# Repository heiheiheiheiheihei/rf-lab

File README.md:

# RF-LAB · 百元射频实验室

**丰俭由人:¥100 的固定码侦察包 → ¥999 的全频段工作台。**
一块 ESP32-C3,五个可换射频舱位;同一套命令契约延伸到 **Web / Android / uConsole /
OPPO Watch 2**,与官网共用一套视觉基线([`docs/01-ui.md` §5.1](docs/01-ui.md))。
现役链路是 **YS-RF34DL 315/433 固定码**;CC1101 / NRF24L01 / SI4463 / LR1121、
MQTT 与 Home Assistant 是路线图,不是现货能力。

[**官网 / 配装台(线上)**](https://heiheiheiheiheihei.github.io/rf-lab/) · [**下载 Android APK**](https://github.com/heiheiheiheiheihei/rf-lab/releases/latest/download/rf-lab-android.apk) · [**OPPO Watch 2 客户端**](watch/README.md) · [**下载 Watch APK**](https://github.com/heiheiheiheiheihei/rf-lab/releases/download/watch-v0.1.0/rf-lab-watch.apk) · [本地源](site/index.html) · [文档索引](docs/README.md) · [射频规格](docs/00-mvp.md) · [UI 规格](docs/01-ui.md) · [接线](hardware/README.md) · [官网维护说明](site/README.md)

## ¥100 → ¥999:先买一块能用的板

| 档位 | 预算 | 组成 | 能力 |
|---|---:|---|---|
| 侦察兵 SCOUT | ¥100 | CORE-C3 + YS-RF34DL | 315/433 固定码学习 / 回放(**现役,已上机**) |
| 突击手 ASSAULT | ¥299 | + CC1101 + NRF24L01 + 背板 + 天线包 | Sub-GHz + 2.4G(路线图) |
| 战术组 TACTICAL | ¥599 | + SI4463 + LR1121 + 收纳盒 | 全频段雏形(路线图) |
| 全频段 ALL-IN | ¥999 | 全模块 + FIELD DOCK | 全舱位 / 现场终端(路线图) |

> 价格为**参考物料价**,不含运费与工具;路线图模块未接入现役固件,不能下单即用。
> 交互式配装器:[`site/index.html`](site/index.html);预算/边界/发布说明:[`site/README.md`](site/README.md)。

### 射频模块

| 模块 | 频段 | 接口 | 角色 | 状态 |
|---|---|---|---|---|
| **YS-RF34DL** | 315 / 433 MHz | UART 9600 | 固定码学习 / 回放 | ✅ **现役,上机验证** |
| CC1101 | 300–928 MHz | SPI | Sub-GHz 通用收发 | ○ 路线图,未接入 |
| NRF24L01+ | 2.4 GHz | SPI | 2.4G 私有链路 | ○ 路线图,未接入 |
| SI4463 | 119–1050 MHz | SPI | 远距 / 窄带 | ○ 路线图,未接入 |
| LR1121 | Sub-GHz + 2.4G | SPI | 双频 LoRa / (G)FSK | ○ 路线图,未接入 |

> 配装器可以勾选路线图模块,那是**采购与规划**,不是固件能力。只有 YS-RF34DL 做过上机验证。

## 现役链路

两块板:**ESP32-C3 OLED** + **YS-RF34DL** 315/433 编解码模块。
按一下原遥控器 → 模块解码 → ESP32 存码 → 板载 OLED 显示状态 → **Web / BLE / 串口 / uConsole**
发射 → 原接收器动作。

硬件文档与官网视觉是**抽象接线图**(不画 3D/写实 PCB):只保留两块功能块、4 根线和必须正确的引脚;
可选的 PCB 底板另见 [`hardware/pcb/`](hardware/pcb/README.md)(已出 Gerber,未打样)。
唯一源是 [`hardware/wiring.json`](hardware/wiring.json);`tools/gen_wiring.py` 同时生成
`firmware/src/wiring_config.h`、`hardware/README.md` / `docs/00-mvp.md` 的接线表和
4 张 SVG,`gen_wiring.py --check` 在主机测试与固件构建前校验一致性。
官网 §01 用宽图(窄屏切竖图)、§02 放主控/模块引脚图;设备 UI 顶栏 `HW` 芯片(或按 `H`)
打开同一张图,`ZOOM/FIT` 缩放。
**3.3V ONLY**、共地、`GPIO3→RXD` / `GPIO4←TXD` 由接线表保证;图不是比例图,
引脚/供电仍以 [`hardware/README.md`](hardware/README.md) 为准。参考照片不入库。

同一块 C3 现在同时提供:

| 入口 | 形态 | 说明 |
|---|---|---|
| **Web** | LAN IP(STA)或 `http://192.168.4.1/`(AP 回退) | 板载 HTTP + SSE,手机/PC/uConsole 浏览器直接用 |
| **Android** | BLE APK | 同一份单页 UI 跑在 WebView,原生 BLE 桥 |
| **OPPO Watch 2** | 独立 BLE APK | 402×476 单屏;ARM → SEND;按住 HOLD → LONG,松手 STOP;46mm 真机已验证 |
| **uConsole** | 键盘 TUI | `rflab-tui`,HTTP 优先、USB 串口回退,琥珀/橄榄战术风 |
| **串口** | `tools/rf34dl.py` | 0.5.0 既有命令行,行为不变 |

### 手腕上的发射键

OPPO Watch 2 客户端把手机端的「选码 → ARM → SEND」压缩成一屏:码卡上下滑换码,
`SEND` 单发,`HOLD` 按住 350ms 才发 `LONG`、松手立刻 `STOP`;断链/退后台先停。
它只走 BLE,复用同一套 GATT/行协议,**不改固件、不改手机 APP**。

- 46mm `OW20W1` / Android 8.1 (API 27) / 402×476 @320dpi 真机已验证:安装、扫描、
  PIN、32 码、ARM/SEND、HOLD/LONG/STOP、错误 PIN、退后台 STOP、OLED TEST。
- 独立 **release key** 签名(不与手机 APK 共用);debug → release 需卸载后重装。
- 公开 Release:[**下载 rf-lab-watch.apk**](https://github.com/heiheiheiheiheihei/rf-lab/releases/download/watch-v0.1.0/rf-lab-watch.apk) ·
  [`SHA256SUMS.txt`](https://github.com/heiheiheiheiheihei/rf-lab/releases/download/watch-v0.1.0/SHA256SUMS.txt)
- 规格与安装:[`watch/README.md`](watch/README.md) · 证据:[`docs/evidence/2026-11-22-watch-release.md`](docs/evidence/2026-11-22-watch-release.md)

**Wi-Fi 模式**:有凭据先 `STA-only` 接局域网(AP 关闭);15s 连不上自动打开 AP 回退;
AP 下可以直接用,也可以重新配网或 `WIFI CLEAR`。AP 里配网成功会保持 AP,避免踢掉
正在配网的浏览器;下次启动再回到 STA-only。

- **射频/命令唯一规格**:[`docs/00-mvp.md`](docs/00-mvp.md)
- **跨平台 UI 规格**:[`docs/01-ui.md`](docs/01-ui.md)
- **接线**:[`hardware/README.md`](hardware/README.md)(模块 4 根线;引脚权威)
- **固件**:[`firmware/README.md`](firmware/README.md)(ESP-IDF 5.5.5 / ESP32-C3)
- **Android**:[`android/README.md`](android/README.md) · **uConsole**:[`uconsole/README.md`](uconsole/README.md) · **Watch**:[`watch/README.md`](watch/README.md)

## 官网 / 配装台

线上:<https://heiheiheiheiheihei.github.io/rf-lab/>(GitHub Pages / GitHub Actions 发布 `site/`)。

[`site/index.html`](site/index.html) 是静态单页:4 档预算、9 个模块勾选、实时配装单、
**内嵌真实单页 UI 的交互终端 demo**、OPPO Watch 2 实机区、MQTT/HA 路线图。
无站点构建、无外部字体、无 CDN、无外部/API 请求。

§03 终端区直接跑 `web/` 的真实 UI(iframe):可以 ARM、SEND、LONG、STOP、ERASE,也可以用
「模拟遥控器」学习一条新码;`site/assets/terminal-demo.js` 在 iframe 内接管
`fetch`/`EventSource`,本地回放 `/api/*` 与 SSE,只标 `SIM`,不发网络请求、不代表真机在线。

```bash
python3 tools/gen_wiring.py --check    # JSON -> 代码头/表/SVG 一致性
python3 tools/build_web.py             # 同步生成 site/assets/terminal.html
python3 -m http.server 8088 -d site    # http://127.0.0.1:8088/
python3 tools/site_check.py            # 静态验收(含 demo 资源)
node --check site/app.js
node --check site/assets/terminal-demo.js
```

## 快速开始

```bash
export PATH="$HOME/.platformio/penv/bin:$PATH"

# 1) 构建 + 烧录(必须用 flash.sh:它会一起写 2MB 分区表)
./tools/flash.sh /dev/ttyACM0

# 2) Web:
#    有 STA 凭据:设备先连局域网;成功用串口 INFO / OLED 显示的 LAN IP 访问。
#    无凭据或 15s 连不上:连 AP "RF-Lab-XXXX" / 密码 rflab1234,打开 http://192.168.4.1/
#    AP 设置页填 SSID/PASSWORD 配网;FORGET/AP 清除凭据。
#    串口会打印 AP SSID/IP、BLE PIN;OLED 开机页也显示 PIN / LAN / AP 状态。

# 3) 串口交互(既有)
python3 tools/rf34dl.py --port /dev/ttyACM0
python3 tools/rf34dl.py --port /dev/ttyACM0 learn 15
python3 tools/rf34dl.py --port /dev/ttyACM0 send 1

# 4) uConsole 键盘 TUI
./uconsole/install.sh
rflab-tui --url http://192.168.4.1   # 若已接 LAN,换成 INFO/OLED 的 LAN IP

# 5) Android(已装 JDK/SDK/Gradle 时)
python3 tools/build_web.py
cd android && ./gradlew assembleDebug

# 6) OPPO Watch 2(独立 release key,见 watch/README.md)
set -a; . "$HOME/.config/rf-lab/watch-keystore.env"; set +a
./watch/check.sh
cd watch && ../android/gradlew assembleRelease
# android/app/build/outputs/apk/debug/app-debug.apk
```

主机单测:`./tools/host_test.sh`(协议 76 + 码库 368 + 事件环 9,427 + OTA 41 + radio 114 + OLED/UI 1,286 + TUI 12)。
APP 自更新逻辑主机测试:`./tools/app_update_test.sh`(版本比较 + `SHA256SUMS` 查表,36 checks)。
Wi-Fi 回退上机自检:`python3 tools/wifi_selftest.py --port /dev/ttyACM0`(15 项)。

## 状态

| 项 | 状态 |
|---|---|
| 构建 | ✅ v0.7.2 tag `e0f155a`:**1,126,928B / 2,031,616B(55.5%)**,RAM 90,260B(27.5%);master M1a(`f55126f`):**1,128,400B(55.5%)**,RAM 90,308B(27.6%),未上机 |
| 主机单测 | ✅ C 测试 **11,312** checks(协议 76 + 码库 368 + 事件环 9,427 + OTA 41 + radio 114 + OLED/UI 1,286);另有 TUI 12、selftest 18、APP 自更新 36 |
| 上机:学码 / 存码 / 改波特率 | ✅ 2026-11-15(0.5.0 证据) |
| 上机:发射 `SEND/LONG/STOP` | ⚠️ 2026-11-15 有 `F0/FE/FF`;2026-11-21 模块命令方向 0 应答;11-22 `MODE` 回 `F2`,但 **`SEND` 未复测** |
| 上机:Wi-Fi | ✅ 真实 `SSID-A`→`192.168.5.117`;AP 回退 15/15;AP 配网 / `WIFI CLEAR`;⏳ AP 外部浏览器、STA 运行中掉线 |
| 上机:Web | ✅ HTTP/SSE/POST + 真实 Chromium 无 console error;⏳ 新皮肤全量回归 |
| 上机:BLE | ✅ 真机连接/鉴权/命令回显/码表/状态栏(2026-11-21);⏳ BLE `SEND`、错误 PIN |
| Android APK | ✅ **0.7.2 已发** [Release](https://github.com/heiheiheiheiheihei/rf-lab/releases/tag/v0.7.2);1,050,272B/versionCode 4/v2;✅ 0.7.1 真机安装/自更新;⏳ 0.7.2 真机安装 |
| APP 自更新 | ✅ 36 checks + 真实 Release 资产;✅ 真机弹窗/下载/系统安装器/覆盖安装(0.7.0→0.7.1);⏳ 失败路径 |
| 码库 v2 | ✅ 21/64;迁移/UTF-8/新建/编辑/删除;✅ BLE `NAME/GROUP/SYM/EDIT` 写入;⏳ 写后重启持久化 |
| OTA | ✅ 双槽 A→B→A + 错 token/坏镜像/断流;⏳ 浏览器上传、崩溃回滚、AP、真断电 |
| uConsole TUI | ✅ 主机解析/键位/PTY;⏳ 真机 |
| 官网 | ✅ 交互 demo + Pages 部署;⏳ 线上交互回归 |
| 官网 APK 入口 | ✅ 指向 `releases/latest/download`;⏳ 真机下载安装 |
| UI 一键固件更新(0.7.3) | ○ **未实现**;BOOT 确认 + GitHub Pages + 设备 SHA-256;见 [`docs/01-ui.md`](docs/01-ui.md) §3.4.1 |
| 路线图 | ○ MQTT / HA / 多模块未实现,接口草案见官网 §04 |
| 距离 / 长发时接收器 | ⏳ 未测,见规格 §7 |
| 上机证据 | [`2026-11-22-release-0.7.2.md`](docs/evidence/2026-11-22-release-0.7.2.md) · [`2026-11-22-app-ble.md`](docs/evidence/2026-11-22-app-ble.md) · [`2026-11-21-ota.md`](docs/evidence/2026-11-21-ota.md) · [`2026-11-15-bringup.md`](docs/evidence/2026-11-15-bringup.md) · [`2026-11-15-wifi-lan.md`](docs/evidence/2026-11-15-wifi-lan.md) |

> 完整测试登记、优先级与 gate 见 [`docs/02-plan.md`](docs/02-plan.md) §3;新会话交接见 [`docs/03-execution.md`](docs/03-execution.md)。

## 范围

| 做 | 不做 |
|---|---|
| 315/433 固定码学习 / 解码 / 存 / 发 | 滚动码克隆 / 重放 |
| 单次发射、长发 / 停止 | 原始 OOK 波形记录(0.7.x) |
| 码库命名/分组/手工建码/改 band+4B code | 协议位解析 / 模块 TX 时长编辑 / `.sub` 导入(0.7.x;0.8.x 只读见 ADR-003) |
| 改模块波特率 / 输出模式 | 扫频 / RSSI / 频谱 |
| Wi-Fi STA 接 LAN + AP 回退(HTTP + SSE) | 公网/云账户 |
| 双槽 OTA(Web/串口,整包含页面) | BLE 上传固件 / 云推送 / 固件签名校验 |
| APP 自更新(GitHub Release,一键/忽略) | 静默安装 / 应用商店分发 |
| BLE 外设 + Android APP | BLE 链路加密(只有应用层 PIN) |
| uConsole 键盘 TUI | OLED 菜单/按键交互 |
| 串口 / OLED 状态页(既有,保留) | OLED 中文/图形界面 |
| 官网 / ¥100–999 配装规划(静态) | 把配装器里的路线图模块写成已支持 |
| 自有固定码设备的复制验证 | 对未知设备的"安全"断言 |

> ⚠️ 固定码本身可被复制:测试只对**自有**设备做,结论只对固定码成立。
> Web 的 `ARM` 只防误触,不是发射硬门控;**HTTP 无登录,AP 密码/局域网可达性是门槛**;
> BLE 只有 4 位应用层 PIN,不是强安全边界。

## 版本计划

| 版本 | 目标 | 状态 |
|---|---|---|
| 0.7.3 | UI 一键固件更新:查 Pages manifest、BOOT 确认、下载/校验/上传 | ○ 规划,见 [`docs/01-ui.md`](docs/01-ui.md) §3.4.1 |
| 0.8.0 | 模块抽象层 + SPI 背板;CC1101 首发,NRF24/SI4463/LR1121 分批(0.8.x) | ○ 设计目标;M1a HAL 仅主机/构建 |
| 0.9.0 | 本地 MQTT bridge + Home Assistant Discovery | ○ 设计目标 |
| 1.0 | 多模块外壳 / 小批量 | ○ 设计目标 |

> 官网 §04 的 MQTT / HA 拓扑与 topic 是**接口草案**,不是可售能力。
> 现在只有 HTTP/SSE + BLE/串口;不要提前写“支持 Home Assistant”。

## 截图

官网 §03 的交互终端(真实单页 UI,传输为本地模拟):

设备 UI 的硬件模态(本地 Chromium mock)与真实 LAN 页面(0.6.0 旧皮肤,非 mock):

更多 mock 布局图在 [`docs/evidence/`](docs/evidence/);截图不是上机证据,上机结论只以 evidence 的 md/log 为准。

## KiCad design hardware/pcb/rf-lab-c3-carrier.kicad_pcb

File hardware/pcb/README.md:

# RF-Lab C3 底板 v1.0

**状态:设计完成、DRC/ERC 通过、Gerber 已导出;未打样、未上机。** 2026-11-23

一块 60 × 80 mm、2 层、全直插的“插座底板”,把现在用杜邦线吊着的
**01Space ESP32-C3-0.42LCD** 和 **YS-RF34DL 315/433 MHz 模块**固定成两块可插拔的板:
C3 板插在左侧 2×7/8 母座上,射频模块插在 J3 母座上,两者都能直接拔换。

> 尺寸在嘉立创免费打板范围内(≤100×100 mm、2 层、绿油、HASL、5 片)。
> **打样前务必打印 [`fab/check-1to1.pdf`](fab/check-1to1.pdf) 按 100% 比例,把 C3 板压上去核对插座孔位。**

| 项目 | 值 |
|---|---|
| 板尺寸 | 60.0 × 80.0 mm,2 层,1.6 mm,1 oz |
| 工艺 | 绿油白字、HASL、无铅(嘉立创免费档) |
| 连接器 | 全 2.54 mm 直插;J1/J2/J3 母座,J4/J5 公排针 |
| 安装 | 4 × M2.5 NPTH(2.7 mm),2 × 2.1 mm 天线/扎带孔 |
| 供电 | 仅 3.3 V;由 C3 板的 3V3 引脚供给模块,板上无稳压器 |
| 额外 | C1 10 µF + C2 100 nF(0805,3V3 去耦,可选) |
| 铜 | 双面 GND 铺铜 + 10 个缝合过孔;信号/电源走线 0.25–0.5 mm |

## 1. 它解决什么问题

现役接法是 C3 板 + 4 根杜邦线 + 模块,换模块/换板都要重新插线,还容易把
VCC/GND 插反。底板把 4 根线固化:

- **C3 板可拔**:两个标准 2.54 母座(1×7 + 1×8),不用焊死在底板上。
- **模块可拔**:J3 是 1×4 母座,模块直接插;旁边 J4 再引一组同样的
  `3V3/GND/IO3/IO4`,接别的串口模块时不用改板。
- **所有剩余 GPIO 引出**:J5(1×16)把 11 个 GPIO 和 3V3/5V/BAT/GND 全部引出。
- **嘉立创免费档**:60×80 mm、2 层、全直插,不需要 SMT 贴片。

## 2. 接口与引脚

### 2.1 C3 插座 J1 / J2(面向底板,USB 朝上)

| 位置 | 1 | 2 | 3 | 4 | 5 | 6 | 7 | 8 |
|---|---|---|---|---|---|---|---|---|
| **J1(8 pin,右列)** | BAT | 5V | GND | 3V3 | IO20 | IO21 | IO0 | IO1 |
| **J2(7 pin,左列)** | IO10 | IO8 | IO7 | IO6 | IO5 | IO4 | IO3 | — |

- 两排**中心距 15.24 mm**(6 × 2.54),针距 2.54;两排**在 Qwiic 端对齐**,
  8 pin 排在 USB 端多出一针 —— 与 01Space 原板一致。
- J1/J2 的 **1 脚是方焊盘**,靠 USB 端;插反了 C3 板的 BAT 会落到 5V 上。
- 丝印已把每一针的网名印在插座外侧;插上 C3 板后仍可见。

### 2.2 模块座 J3(1×4 母座)

| 针 | 1 | 2 | 3 | 4 |
|---|---|---|---|---|
| 网名 | **3V3** | **IO4** | **IO3** | **GND** |
| 模块侧 | VCC | TXD | RXD | GND |

模块的 4 针顺序按你确认的 **VCC → TXD → RXD → GND**(从正面、天线端数)。
交叉关系:**模块 TXD(2)→ C3 的 IO4(RX)**,**模块 RXD(3)← C3 的 IO3(TX)**。

> **接反 VCC/GND 会烧模块。** 上电前用万用表量 J3.1–J3.4 应为 3.3 V;
> 若你的模块丝印顺序不是 VCC/TXD/RXD/GND,**不要插 J3**,改用 J4 飞线。

### 2.3 备用座 J4(1×4 公排针)

| 针 | 1 | 2 | 3 | 4 |
|---|---|---|---|---|
| 网名 | 3V3 | GND | IO3 | IO4 |

### 2.4 全引出 J5(1×16 公排针)

| 针 | 1 | 2 | 3 | 4 | 5 | 6 | 7 | 8 |
|---|---|---|---|---|---|---|---|---|
| 网名 | IO3 | IO4 | IO5 | IO6 | IO7 | IO8 | IO10 | GND |

| 针 | 9 | 10 | 11 | 12 | 13 | 14 | 15 | 16 |
|---|---|---|---|---|---|---|---|---|
| 网名 | IO1 | IO0 | IO21 | IO20 | 3V3 | 5V | BAT | GND |

- 1 脚方焊盘在**左侧**(靠近 J2)。
- 11 个 GPIO 全部引出;IO20/IO21 同时是 UART0 控制台,引出不影响现役固件。
- **BAT 是电池输入脚**,不是稳压输出;不要把它当 3.3 V 源。

### 2.5 与 `hardware/wiring.json` 的关系

`gen_pcb.py` 启动时会读 `../wiring.json`,断言 `module_tx=3`、`module_rx=4`、
`console=20/21`、`oled=5/6`;改接线先改 JSON,再重跑生成器。PCB 的 4 根模块线
不是第二套定义。

## 3. BOM(全部可手焊)

| 位号 | 规格 | 数量 | 备注 |
|---|---|---|---|
| J1 | 2.54 mm 1×8 **母座** | 1 | 可用 1×40 排母剪 |
| J2 | 2.54 mm 1×7 **母座** | 1 | 同上 |
| J3 | 2.54 mm 1×4 **母座** | 1 | 模块座 |
| J4 | 2.54 mm 1×4 **公排针** | 1 | 备用模块口 |
| J5 | 2.54 mm 1×16 **公排针** | 1 | 全引出 |
| C1 | 10 µF 16 V X5R 0805 | 1 | 可选,3V3 储能 |
| C2 | 100 nF 50 V X7R 0805 | 1 | 可选,去耦 |
| H1–H4 | M2.5 螺丝/铜柱 | 4 | 2.7 mm 孔 |
| — | 17–23 cm 单芯天线 | 1 | 焊在模块天线焊盘 |

CSV:[`fab/bom.csv`](fab/bom.csv)。

## 4. 装配顺序

1. 先焊 J1、J2、J3 三个**母座**,再焊 J4、J5 两个公排针;最后焊 C1/C2(可选)。
2. 断电,万用表检查:
   - J3.1–J3.4 之间**不能短路**;
   - J1.3(GND)与 J1.4(3V3)之间不能短路;
   - J5.8 / J5.16 与 J1.3 通。
3. 把 C3 板插进 J1/J2:**USB 朝底板的上边缘**,J1 的方焊盘对 C3 的 BAT 针。
4. 上电(USB),量 J3.1 对 J3.4 应为 **3.3 V**。
5. 断电,插模块(J3.1=VCC),接天线,再上电。
6. 用 `INFO` / 串口确认模块有应答;第一次不要直接长发射。

**禁止**:5 V 进 J3.1 或 C3 的 GPIO;不接天线长时间发射;带电插拔模块。

## 5. 嘉立创免费打板

1. 打开 [嘉立创下单页](https://www.jlc.com/) / 嘉立创下单助手,选 **PCB 下单**。
2. 上传 [`fab/rf-lab-c3-carrier-gerbers.zip`](fab/rf-lab-c3-carrier-gerbers.zip)(46 KB,
   含 7 个 Gerber(铜/阻焊/丝印/板框)+ PTH/NPTH 两个钻孔文件 + gbrjob)。
3. 参数:
   - 层数 **2**,尺寸自动识别 **60 × 80 mm**;
   - 板厚 **1.6 mm**,铜厚 **1 oz**,材质 FR-4;
   - 阻焊 **绿色**,丝印 **白色**,表面处理 **HASL(有铅/无铅按活动)**;
   - 数量 **5**,“PCB 只做板,不贴片”。
4. 免费档通常要求:**≤100×100 mm、2 层、1.6 mm、绿油、HASL、5 片**;
   板费可免,**运费和加急/彩色/沉金另计**,以当期活动为准。
5. 下单前预览生产稿:确认 **板框 60×80、4 个 M2.5 孔、2 个天线孔、J1/J2 两排孔**都在。
6. **首件先打 1:1 纸样**:打印 [`fab/check-1to1.pdf`](fab/check-1to1.pdf),打印设置选
   **100% / 实际大小**(不要“适合页面”)。纸样页尺寸 60.1×80.1 mm;把 C3 板压上去,
   15 个插座孔应一一对齐。对不上就先别下单。

## 6. 设计验证(证据)

| 项 | 结果 | 命令/文件 |
|---|---|---|
| PCB DRC | **0 violations,0 unconnected** | `kicad-cli pcb drc --severity-all --exit-code-violations` |
| 原理图 ERC | **0 电气错误**,7 条 `lib_symbol_issues` 警告(符号已内嵌,仅库名未注册) | `kicad-cli sch erc` |
| Gerber | 7 个 Gerber + PTH 52 孔 + NPTH 6 孔,zip 46 KB | `fab/rf-lab-c3-carrier-gerbers.zip` |
| 1:1 纸样 | 170.35 × 227.02 pt = 60.1 × 80.1 mm | `fab/check-1to1.pdf` |
| 丝印/焊盘预览 | 顶层/底层/原理图 | `img/top.png`、`img/bottom.png`、`img/schematic.pdf` |
| 打样 | **未做** | — |
| 上机(插拔/供电/发射/距离) | **未做** | — |

SHA-256:

```
a2909ef3eff3edc911d390ac7712ad322066cf0819f7020652b548c484943c95  fab/rf-lab-c3-carrier-gerbers.zip
d51fd27e1226e4d33e344f1fc7a35ffdb994b9f916809e6ab2423b5f49403b70  fab/check-1to1.pdf
623c9621dbc854c5b6c486045d6c309e7fdff08ec2e7a44094ed4ec66d6920f8  rf-lab-c3-carrier.kicad_pcb
```

## 7. 风险与未验证项(★ 打样前看)

| # | 风险 | 后果 | 处理 |
|---|---|---|---|
| 1 | **C3 插座跨距按 15.24 mm 画**;不同批次/克隆板可能是 16 或 17.78 mm | 插不进去 | 先打 1:1 纸样;若实测不同,需要改布局重画(不是改一个数) |
| 2 | **模块 4 针顺序按 VCC/TXD/RXD/GND** | 接反烧模块 | 上电前量 J3.1–J3.4;不确定就用 J4 飞线 |
| 3 | 5 V 直接进 3V3/GPIO | 烧模块/烧 C3 | 板上丝印 `3.3V ONLY / 5V = DAMAGE`;无 5 V 输入口 |
| 4 | 无电源开关、无防反接、无电平转换 | 模块常带电;5 V 模块需另做电平 | 不用时拔 USB;5 V 改造见 `hardware/README.md` §4 |
| 5 | 模块悬在 J3 上,只有 4 根针受力 | 反复插拔/拉天线会松 | 用 ANT/ZIP 孔扎带固定模块和天线 |
| 6 | 免费打板是活动/优惠券,不是永久 | 下单时可能收费 | 以嘉立创当期活动为准;板费之外还有运费 |
| 7 | 0805 C1/C2 接在整片 GND 铜上 | 手焊散热快 | 可先不焊;需要时用烙铁+助焊剂或热风 |
| 8 | 未做 EMC/ESD/射频匹配 | 433 MHz 距离未验证 | 只做载体,射频性能取决于模块和天线 |

## 8. 设计与取舍(为什么这样)

- **用两个标准母座而不是画 C3 的定制封装**:C3 板可拔换、母座便宜、坏了好换;
  代价是必须精确知道两排针的跨距(见风险 1)。
- **J5 用 1×16 单排,不用 2×8**:单排每根信号都从上方进针,两组扇出
  (J2 左侧 7 根、J1 右侧 8 根)不交叉;2×8 的第二排会被第一排挡住。
- **双面 GND 铺铜 + 实心连接**:DRC 干净、回流短;代价是 0805 焊盘散热快。
- **5V/BAT 走底层、IO3/IO4 到 J4 走底层**:顶层丝印和 C3 扇出保持干净。
- **全直插 + 0805 可选**:嘉立创只做板,不产生 SMT 费用;0805 手焊难度可接受。
- **J3 的 TXD/RXD 交叉在板上完成**:模块 TXD→IO4、RXD←IO3,插上就是交叉,
  不需要再记杜邦线怎么接。

## 9. 重新生成

```bash
cd hardware/pcb
python3 gen_pcb.py                 # 生成未铺铜的 .kicad_pcb
./fill_zones.sh rf-lab-c3-carrier.kicad_pcb   # KiCad 9.0.8 无头铺铜(见下)
python3 gen_sch.py                 # 生成 .kicad_sch
kicad-cli pcb drc --severity-all --exit-code-violations rf-lab-c3-carrier.kicad_pcb
kicad-cli pcb export gerbers -o fab/gerbers/ -l F.Cu,B.Cu,F.Paste,B.Paste,F.Silkscreen,B.Silkscreen,F.Mask,B.Mask,Edge.Cuts --no-x2 rf-lab-c3-carrier.kicad_pcb
kicad-cli pcb export drill -o fab/gerbers/ --format excellon --drill-origin absolute --excellon-units mm --excellon-zeros-format decimal --excellon-separate-th rf-lab-c3-carrier.kicad_pcb
```

> **不要在 KiCad 里“从原理图更新 PCB”。** 这块板的布局/走线由 `gen_pcb.py`
> 生成,原理图(`gen_sch.py`)只是同一组网名的可读视图;直接 Update 会把走线冲掉。
> 要改布局,改 `gen_pcb.py` 后重跑上面两条,再重新铺铜。

**为什么要 `fill_zones.sh`**:本机 KiCad 9.0.8 的 Python `ZONE_FILLER` 在没有
`PCB_EDIT_FRAME` 时会段错误;脚本用 `xvfb-run` 起真正的 pcbnew,按 `B` 铺铜、
`Ctrl+S` 保存。需要 `xvfb`、`xdotool`。改完布局后必须重新铺铜,否则 Gerber 里
只有空的铜皮轮廓。

## 10. 文件

| 文件 | 内容 |
|---|---|
| [`rf-lab-c3-carrier.kicad_pcb`](rf-lab-c3-carrier.kicad_pcb) | 已铺铜的 KiCad 9 PCB |
| [`rf-lab-c3-carrier.kicad_sch`](rf-lab-c3-carrier.kicad_sch) | 单页原理图(网名标注式) |
| [`gen_pcb.py`](gen_pcb.py) | PCB 生成器(布局/走线/丝印/铺铜) |
| [`gen_sch.py`](gen_sch.py) | 原理图生成器 |
| [`fill_zones.sh`](fill_zones.sh) | 无头铺铜脚本 |
| [`fab/rf-lab-c3-carrier-gerbers.zip`](fab/rf-lab-c3-carrier-gerbers.zip) | **嘉立创上传用** |
| [`fab/check-1to1.pdf`](fab/check-1to1.pdf) | **1:1 纸样**,打印后核对插座 |
| [`fab/bom.csv`](fab/bom.csv) | 手焊 BOM |
| [`img/top.png`](img/top.png) / [`img/bottom.png`](img/bottom.png) | 顶层/底层预览 |
| [`img/schematic.pdf`](img/schematic.pdf) | 原理图 PDF |

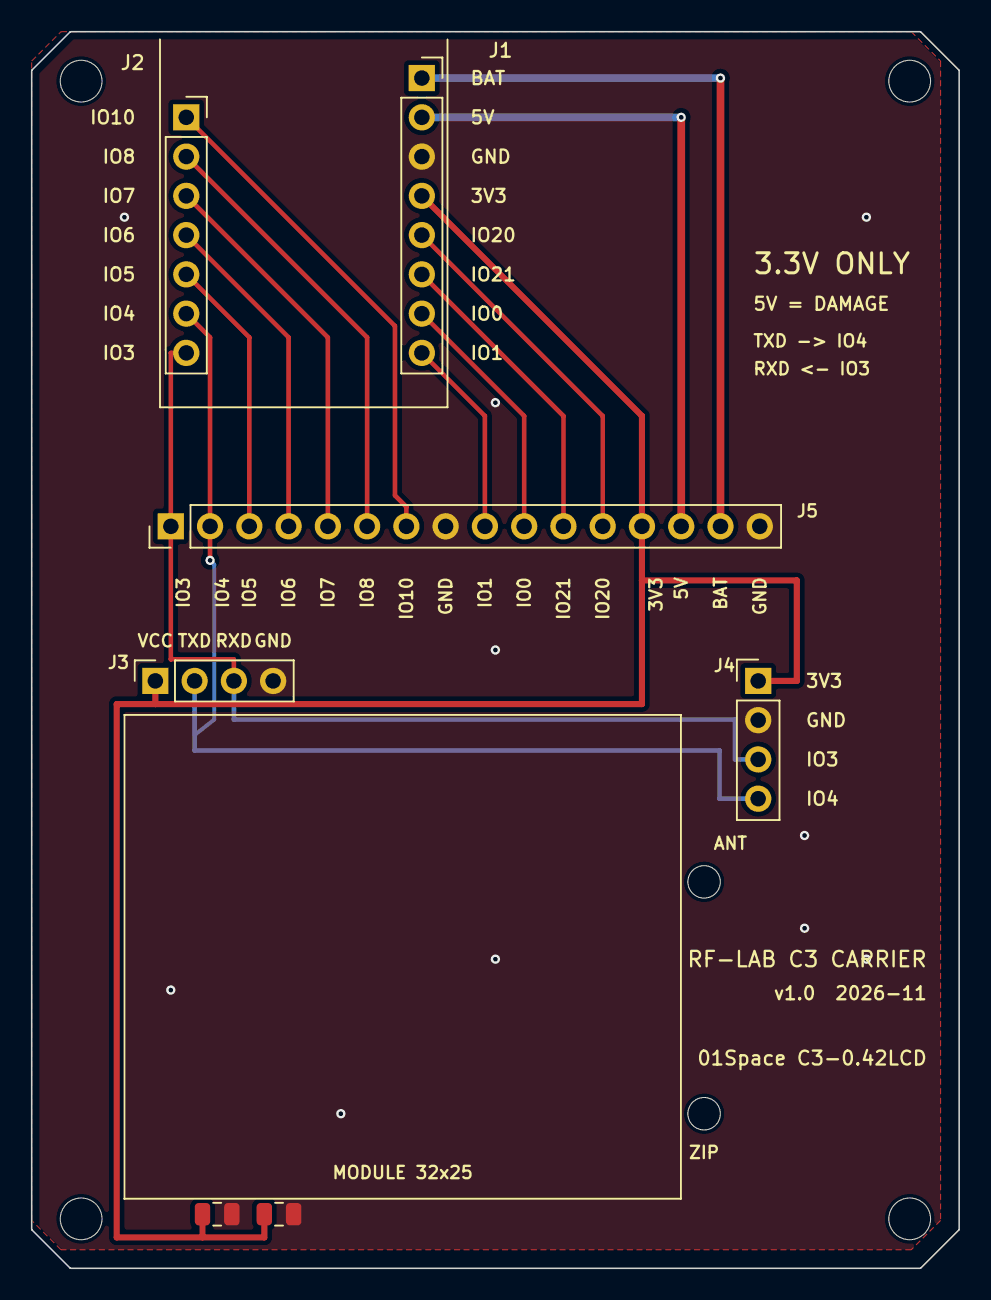
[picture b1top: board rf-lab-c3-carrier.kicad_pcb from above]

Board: 2 copper layers, 60.0 x 80.0 mm, 13 parts (0 on the bottom side), 15 nets.

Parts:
ANT1, ANT2: MountingHole_2.1mm
C1, C2: C_0805_2012Metric
H1, H2, H3, H4: MountingHole_2.7mm_M2.5
J1: PinSocket_1x08_P2.54mm_Vertical
J2: PinSocket_1x07_P2.54mm_Vertical
J3: PinSocket_1x04_P2.54mm_Vertical
J4: PinHeader_1x04_P2.54mm_Vertical
J5: PinHeader_1x16_P2.54mm_Vertical

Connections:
3V3: C1.1, C2.1, J1.4, J3.1, J4.1, J5.13
5V: J1.2, J5.14
BAT: J1.1, J5.15
GND: C1.2, C2.2, J1.3, J3.4, J4.2, J5.8, J5.16
IO0: J1.7, J5.10
IO1: J1.8, J5.9
IO3: J2.7, J3.3, J4.3, J5.1
IO4: J2.6, J3.2, J4.4, J5.2
IO5: J2.5, J5.3
IO6: J2.4, J5.4
IO7: J2.3, J5.5
IO8: J2.2, J5.6
IO10: J2.1, J5.7
IO20: J1.5, J5.12
IO21: J1.6, J5.11

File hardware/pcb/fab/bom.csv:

Comment,Designator,Footprint,Qty,Note
2.54mm 1x8 female socket,J1,Connector_PinSocket_2.54mm:PinSocket_1x08_P2.54mm_Vertical,1,C3 carrier row A
2.54mm 1x7 female socket,J2,Connector_PinSocket_2.54mm:PinSocket_1x07_P2.54mm_Vertical,1,C3 carrier row B
2.54mm 1x4 female socket,J3,Connector_PinSocket_2.54mm:PinSocket_1x04_P2.54mm_Vertical,1,YS-RF34DL socket
2.54mm 1x4 male header,J4,Connector_PinHeader_2.54mm:PinHeader_1x04_P2.54mm_Vertical,1,spare module header
2.54mm 1x16 male header,J5,Connector_PinHeader_2.54mm:PinHeader_1x16_P2.54mm_Vertical,1,GPIO breakout
10uF 16V X5R 0805,C1,Capacitor_SMD:C_0805_2012Metric,1,3V3 bulk (optional)
100nF 50V X7R 0805,C2,Capacitor_SMD:C_0805_2012Metric,1,3V3 decoupling (optional)
M2.5 screw + nut/standoff,H1 H2 H3 H4,,4,2.7mm NPTH
Antenna zip-tie point,ANT1 ANT2,,2,2.1mm NPTH
